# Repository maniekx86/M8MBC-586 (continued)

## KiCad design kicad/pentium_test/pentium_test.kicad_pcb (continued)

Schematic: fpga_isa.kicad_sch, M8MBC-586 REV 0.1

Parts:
C801, C802, C803, C804, C805, C806, C807, C808, C809, C810, C811, C815, C816, C817, C818, C819, C820: 100n; C_0603_1608Metric
C812, C813, C814: 1u; C_0805_2012Metric
C821, C822: 4.7u; C_0603_1608Metric
C823: 22u; C_1206_3216Metric
C824: 47u; CP_Radial_D5.0mm_P2.50mm
R801, R802: 33; R_0603_1608Metric
TP801: FPGA_ISA_SPARE1; TestPoint_Pad_D1.0mm
TP802: FPGA_ISA_SPARE6; TestPoint_Pad_D1.0mm
TP803: FPGA_ISA_SPARE2; TestPoint_Pad_D1.0mm
TP804: FPGA_ISA_SPARE7; TestPoint_Pad_D1.0mm
TP805: FPGA_ISA_SPARE3; TestPoint_Pad_D1.0mm
TP806: FPGA_ISA_SPARE8; TestPoint_Pad_D1.0mm
TP807: FPGA_ISA_SPARE4; TestPoint_Pad_D1.0mm
TP809: FPGA_ISA_SPARE5; TestPoint_Pad_D1.0mm
TP810: ISA_VCCINT; TestPoint_Pad_D1.0mm
U801: XC6SLX9-FTG256; Xilinx_FTG256
U802: LDL1117S12R; SOT-223-3_TabPin2
Y801: 14.318 MHz; Crystal_SMD_7050-4Pin_7.0x5.0mm

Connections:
+1V2_F3: C817.1, C818.1, C819.1, C820.1, C821.1, C822.1, C823.1, C824.1, TP810.1, U801.G7 (VCCINT), U801.G9 (VCCINT), U801.H8 (VCCINT), U801.H10 (VCCINT), U801.J7 (VCCINT), U801.J9 (VCCINT), U801.K8 (VCCINT), U801.K10 (VCCINT), U802.2 (VO)
+3V3: C801.1, C802.1, C803.1, C804.1, C805.1, C806.1, C807.1, C808.1, C809.1, C810.1, C811.1, C812.1, C813.1, C814.1, C815.1, C816.1, U801.B4 (VCCO_0), U801.B9 (VCCO_0), U801.B13 (VCCO_0), U801.D2 (VCCO_3), U801.D7 (VCCO_0), U801.D10 (VCCO_0), U801.D15 (VCCO_1), U801.E5 (VCCAUX), U801.F8 (VCCAUX), U801.F11 (VCCAUX), U801.G4 (VCCO_3), U801.G10 (VCCAUX), U801.G13 (VCCO_1), U801.H6 (VCCAUX), U801.J2 (VCCO_3), U801.J10 (VCCAUX), U801.J15 (VCCO_1), U801.K4 (VCCO_3), U801.K13 (VCCO_1), U801.L6 (VCCAUX), U801.L9 (VCCAUX), U801.N2 (VCCO_3), U801.N7 (VCCO_2), U801.N10 (VCCO_2), U801.N11 (IO_L13P_M1_2), U801.N15 (VCCO_1), U801.R4 (VCCO_2), U801.R8 (VCCO_2), U801.R13 (VCCO_1), U801.T11 (IO_L1N_M0_CMPMISO_2), U802.3 (VI), Y801.4 (Vdd); also elsewhere on the board
/fpga_isa/FPGA_ISA_SPARE1: TP801.1, U801.B3 (IO_L83P_3)
/fpga_isa/FPGA_ISA_SPARE2: TP803.1, U801.A3 (IO_L83N_VREF_3)
/fpga_isa/FPGA_ISA_SPARE3: TP805.1, U801.A2 (IO_L52N_M3A9_3)
/fpga_isa/FPGA_ISA_SPARE4: TP807.1, U801.B2 (IO_L52P_M3A8_3)
/fpga_isa/FPGA_ISA_SPARE5: TP809.1, U801.B1 (IO_L50N_M3BA2_3)
/fpga_isa/FPGA_ISA_SPARE6: TP802.1, U801.C1 (IO_L50P_M3WE_3)
/fpga_isa/FPGA_ISA_SPARE7: TP804.1, U801.C2 (IO_L48N_M3BA1_3)
/fpga_isa/FPGA_ISA_SPARE8: TP806.1, U801.C3 (IO_L48P_M3BA0_3)
/fpga_isa/ISA_FPGA_OSC: R802.2, U801.J16 (IO_L43N_GCLK4_M1DQ5_1)
A20M#: U801.C16 (IO_L33N_A14_M1A4_1); also elsewhere on the board
FPGA_ISA_CCLK: U801.R11 (IO_L1P_CCLK_2); also elsewhere on the board
FPGA_ISA_DIN: U801.P10 (IO_L3P_D0_DIN_MISO_MISO1_2); also elsewhere on the board
FPGA_ISA_DONE: U801.P13 (DONE_2); also elsewhere on the board
FPGA_ISA_INIT: U801.R3 (IO_L65P_INIT_B_2); also elsewhere on the board
FPGA_ISA_PROGRAM: U801.T2 (PROGRAM_B_2); also elsewhere on the board
GND: C801.2, C802.2, C803.2, C804.2, C805.2, C806.2, C807.2, C808.2, C809.2, C810.2, C811.2, C812.2, C813.2, C814.2, C815.2, C816.2, C817.2, C818.2, C819.2, C820.2, C821.2, C822.2, C823.2, C824.2, U801.A1 (GND), U801.A16 (GND), U801.B7 (GND), U801.B11 (GND), U801.D4 (GND), U801.D13 (GND), U801.E9 (GND), U801.G2 (GND), U801.G8 (GND), U801.G15 (GND), U801.H7 (GND), U801.H9 (GND), U801.H12 (GND), U801.J5 (GND), U801.J8 (GND), U801.K7 (GND), U801.K9 (GND), U801.L2 (GND), U801.L15 (GND), U801.M8 (GND), U801.N13 (GND), U801.P3 (GND), U801.P14 (SUSPEND), U801.R6 (GND), U801.R10 (GND), U801.T1 (GND), U801.T16 (GND), U802.1 (GND), Y801.2 (GND); also elsewhere on the board
INIT: U801.A14 (IO_L65N_SCP2_0); also elsewhere on the board
INTR: U801.B16 (IO_L29N_A22_M1A14_1); also elsewhere on the board
ISA_A0: U801.P6 (IO_L47P_2); also elsewhere on the board
ISA_A1: U801.N6 (IO_L64N_D9_2); also elsewhere on the board
ISA_A2: U801.P5 (IO_L49N_D4_2); also elsewhere on the board
ISA_A3: U801.N5 (IO_L49P_D3_2); also elsewhere on the board
ISA_A4: U801.M5 (IO_L2P_3); also elsewhere on the board
ISA_A5: U801.N4 (IO_L2N_3); also elsewhere on the board
ISA_A6: U801.M4 (IO_L1P_3); also elsewhere on the board
ISA_A7: U801.L5 (IO_L45N_M3ODT_3); also elsewhere on the board
ISA_A8: U801.M3 (IO_L1N_VREF_3); also elsewhere on the board
ISA_A9: U801.L4 (IO_L45P_M3A3_3); also elsewhere on the board
ISA_A10: U801.L3 (IO_L36P_M3DQ8_3); also elsewhere on the board
ISA_A11: U801.L8 (IO_L62P_D5_2); also elsewhere on the board
ISA_A12: U801.K3 (IO_L42P_GCLK25_TRDY2_M3UDM_3); also elsewhere on the board
ISA_A13: U801.J4 (IO_L42N_GCLK24_M3LDM_3); also elsewhere on the board
ISA_A14: U801.J3 (IO_L38P_M3DQ2_3); also elsewhere on the board
ISA_A15: U801.K5 (IO_L47P_M3A0_3); also elsewhere on the board
ISA_A16: U801.K6 (IO_L47N_M3A1_3); also elsewhere on the board
ISA_A17: U801.J6 (IO_L43P_GCLK23_M3RASN_3); also elsewhere on the board
ISA_A18: U801.H5 (IO_L43N_GCLK22_IRDY2_M3CASN_3); also elsewhere on the board
ISA_A19: U801.H3 (IO_L44N_GCLK20_M3A6_3); also elsewhere on the board
ISA_AEN: U801.K12 (IO_L42P_GCLK7_M1UDM_1); also elsewhere on the board
ISA_ALE: U801.P12 (IO_L12N_D2_MISO3_2); also elsewhere on the board
ISA_CLK: U801.T13 (IO_L51N_M1DQ13_1); also elsewhere on the board
ISA_D0: U801.P2 (IO_L33P_M3DQ12_3); also elsewhere on the board
ISA_D1: U801.P1 (IO_L33N_M3DQ13_3); also elsewhere on the board
ISA_D2: U801.N3 (IO_L34P_M3UDQS_3); also elsewhere on the board
ISA_D3: U801.N1 (IO_L34N_M3UDQSN_3); also elsewhere on the board
ISA_D4: U801.M1 (IO_L35N_M3DQ11_3); also elsewhere on the board
ISA_D5: U801.J1 (IO_L38N_M3DQ3_3); also elsewhere on the board
ISA_D6: U801.K2 (IO_L37P_M3DQ0_3); also elsewhere on the board
ISA_D7: U801.K1 (IO_L37N_M3DQ1_3); also elsewhere on the board
ISA_D8: U801.L1 (IO_L36N_M3DQ9_3); also elsewhere on the board
ISA_D9: U801.M2 (IO_L35P_M3DQ10_3); also elsewhere on the board
ISA_D10: U801.R1 (IO_L32N_M3DQ15_3); also elsewhere on the board
ISA_D11: U801.R2 (IO_L32P_M3DQ14_3); also elsewhere on the board
ISA_D12: U801.T3 (IO_L65N_CSO_B_2); also elsewhere on the board
ISA_D13: U801.T5 (IO_L48N_RDWR_B_VREF_2); also elsewhere on the board
ISA_D14: U801.T6 (IO_L47N_2); also elsewhere on the board
ISA_D15: U801.R7 (IO_L32P_GCLK29_2); also elsewhere on the board
ISA_DRQ0: U801.J11 (IO_L40P_GCLK11_M1A5_1); also elsewhere on the board
ISA_DRQ1: U801.T10 (IO_L3N_MOSI_CSI_B_MISO0_2); also elsewhere on the board
ISA_DRQ2: U801.R5 (IO_L48P_D7_2); also elsewhere on the board
ISA_DRQ3: U801.M13 (IO_L74P_AWAKE_1); also elsewhere on the board
ISA_DRQ5: U801.L14 (IO_L47P_FWE_B_M1DQ0_1); also elsewhere on the board
ISA_DRQ6: U801.L16 (IO_L47N_LDC_M1DQ1_1); also elsewhere on the board
ISA_DRQ7: U801.K15 (IO_L44P_A3_M1DQ6_1); also elsewhere on the board
ISA_IO_READY: U801.K16 (IO_L44N_A2_M1DQ7_1); also elsewhere on the board
ISA_IRQ2: U801.T4 (IO_L63N_2); also elsewhere on the board
ISA_IRQ3: U801.P8 (IO_L30P_GCLK1_D13_2); also elsewhere on the board
ISA_IRQ4: U801.T8 (IO_L30N_GCLK0_USERCCLK_2); also elsewhere on the board
ISA_IRQ5: U801.R9 (IO_L23P_2); also elsewhere on the board
ISA_IRQ6: U801.T14 (IO_L51P_M1DQ12_1); also elsewhere on the board
ISA_IRQ7: U801.T9 (IO_L23N_2); also elsewhere on the board
ISA_IRQ10: U801.P15 (IO_L48P_HDC_M1DQ8_1); also elsewhere on the board
ISA_IRQ11: U801.N16 (IO_L45N_A0_M1LDQSN_1); also elsewhere on the board
ISA_IRQ12: U801.L13 (IO_L53N_VREF_1); also elsewhere on the board
ISA_IRQ14: U801.M16 (IO_L46N_FOE_B_M1DQ3_1); also elsewhere on the board
ISA_IRQ15: U801.M15 (IO_L46P_FCS_B_M1DQ2_1); also elsewhere on the board
ISA_LA17: U801.M10 (IO_L16N_VREF_2); also elsewhere on the board
ISA_LA18: U801.L7 (IO_L62N_D6_2); also elsewhere on the board
ISA_LA19: U801.P7 (IO_L31P_GCLK31_D14_2); also elsewhere on the board
ISA_LA20: U801.M6 (IO_L64P_D8_2); also elsewhere on the board
ISA_LA21: U801.M7 (IO_L31N_GCLK30_D15_2); also elsewhere on the board
ISA_LA22: U801.N8 (IO_L29N_GCLK2_2); also elsewhere on the board
ISA_LA23: U801.L10 (IO_L16P_2); also elsewhere on the board
ISA_RESET: U801.M9 (IO_L29P_GCLK3_2); also elsewhere on the board
ISA_SBHE: U801.T15 (IO_L50N_M1UDQSN_1); also elsewhere on the board
ISA_SLOT_OSC: R801.2; also elsewhere on the board
ISA_TC: U801.R12 (IO_L52P_M1DQ14_1); also elsewhere on the board
JTAG2_TCK: U801.C14 (TCK); also elsewhere on the board
JTAG2_TDI: U801.C12 (TDI); also elsewhere on the board
JTAG2_TDO: U801.E14 (TDO); also elsewhere on the board
JTAG2_TMS: U801.A15 (TMS); also elsewhere on the board
KEYBOARD_CLK: U801.A8 (IO_L33N_0); also elsewhere on the board
KEYBOARD_DATA: U801.A7 (IO_L6N_0); also elsewhere on the board
MOUSE_CLK: U801.A6 (IO_L4N_0); also elsewhere on the board
MOUSE_DATA: U801.B6 (IO_L4P_0); also elsewhere on the board
NMI: U801.B14 (IO_L65P_SCP3_0); also elsewhere on the board
unnamed: R801.1, R802.1, Y801.3 (OUT)
PCI_AD0: U801.J14 (IO_L43P_GCLK5_M1DQ4_1); also elsewhere on the board
PCI_AD1: U801.J12 (IO_L40N_GCLK10_M1A6_1); also elsewhere on the board
PCI_AD2: U801.H11 (IO_L38N_A4_M1CLKN_1); also elsewhere on the board
PCI_AD3: U801.G11 (IO_L30N_A20_M1A11_1); also elsewhere on the board
PCI_AD4: U801.G12 (IO_L38P_A5_M1CLK_1); also elsewhere on the board
PCI_AD5: U801.H13 (IO_L39P_M1A3_1); also elsewhere on the board
PCI_AD6: U801.F12 (IO_L30P_A21_M1RESET_1); also elsewhere on the board
PCI_AD7: U801.G14 (IO_L36P_A9_M1BA0_1); also elsewhere on the board
PCI_AD8: U801.F13 (IO_L32P_A17_M1A8_1); also elsewhere on the board
PCI_AD9: U801.F10 (IO_L64P_SCP5_0); also elsewhere on the board
PCI_AD10: U801.E13 (IO_L1P_A25_1); also elsewhere on the board
PCI_AD11: U801.E12 (IO_L1N_A24_VREF_1); also elsewhere on the board
PCI_AD12: U801.D14 (IO_L31P_A19_M1CKE_1); also elsewhere on the board
PCI_AD13: U801.F6 (IO_L55P_M3A13_3); also elsewhere on the board
PCI_AD14: U801.C7 (IO_L6P_0); also elsewhere on the board
PCI_AD15: U801.C8 (IO_L38N_VREF_0); also elsewhere on the board
PCI_AD16: U801.D12 (IO_L66N_SCP0_0); also elsewhere on the board
PCI_AD17: U801.D11 (IO_L66P_SCP1_0); also elsewhere on the board
PCI_AD18: U801.C13 (IO_L63P_SCP7_0); also elsewhere on the board
PCI_AD19: U801.E11 (IO_L64N_SCP4_0); also elsewhere on the board
PCI_AD20: U801.G5 (IO_L51N_M3A4_3); also elsewhere on the board
PCI_AD21: U801.F4 (IO_L53P_M3CKE_3); also elsewhere on the board
PCI_AD22: U801.F3 (IO_L53N_M3A12_3); also elsewhere on the board
PCI_AD23: U801.E3 (IO_L54N_M3A11_3); also elsewhere on the board
PCI_AD24: U801.D3 (IO_L49P_M3A7_3); also elsewhere on the board
PCI_AD25: U801.E4 (IO_L54P_M3RESET_3); also elsewhere on the board
PCI_AD26: U801.E6 (IO_L5N_0); also elsewhere on the board
PCI_AD27: U801.G6 (IO_L51P_M3A10_3); also elsewhere on the board
PCI_AD28: U801.D5 (IO_L3P_0); also elsewhere on the board
PCI_AD29: U801.C5 (IO_L3N_0); also elsewhere on the board
PCI_AD30: U801.C6 (IO_L7N_0); also elsewhere on the board
PCI_AD31: U801.D6 (IO_L7P_0); also elsewhere on the board
PCI_PAR: U801.E7 (IO_L36P_GCLK15_0); also elsewhere on the board
PC_SPK: U801.H15 (IO_L37P_A7_M1A0_1); also elsewhere on the board
POWER_REQ: U801.J13 (IO_L41P_GCLK9_IRDY1_M1RASN_1); also elsewhere on the board
RP_SB_LINK_CLK: U801.B5 (IO_L2P_0); also elsewhere on the board
RP_SB_LINK_DATA: U801.A5 (IO_L2N_0); also elsewhere on the board
RTC_AS: U801.H2 (IO_L39P_M3LDQS_3); also elsewhere on the board
SB_CLK: U801.H4 (IO_L44P_GCLK21_M3A5_3); also elsewhere on the board
SB_NB_SPARE: U801.A4 (IO_L1N_VREF_0); also elsewhere on the board
SB_SPARE_1: U801.K14 (IO_L41N_GCLK8_M1CASN_1); also elsewhere on the board
SERIAL_1_CTS: U801.A11 (IO_L39N_0); also elsewhere on the board
SERIAL_1_DCD: U801.A13 (IO_L63N_SCP6_0); also elsewhere on the board
SERIAL_1_DSR: U801.B12 (IO_L62P_0); also elsewhere on the board
SERIAL_1_DTR: U801.A10 (IO_L35N_GCLK16_0); also elsewhere on the board
SERIAL_1_RI: U801.B10 (IO_L35P_GCLK17_0); also elsewhere on the board
SERIAL_1_RTS: U801.A9 (IO_L34N_GCLK18_0); also elsewhere on the board
SERIAL_1_RXD: U801.A12 (IO_L62N_VREF_0); also elsewhere on the board
SERIAL_1_TXD: U801.B8 (IO_L33P_0); also elsewhere on the board
~FERR: U801.D16 (IO_L31N_A18_M1A12_1); also elsewhere on the board
~FPGA_RESET: U801.P4 (IO_L63P_2); also elsewhere on the board
~IDE_CS1FX: U801.G16 (IO_L36N_A8_M1BA1_1); also elsewhere on the board
~IDE_CS3FX: U801.H14 (IO_L39N_M1ODT_1); also elsewhere on the board
~IDE_RESET: U801.H16 (IO_L37N_A6_M1A1_1); also elsewhere on the board
~IDE_TR_DIR: U801.F16 (IO_L35N_A10_M1A2_1); also elsewhere on the board
~IDE_TR_OE: U801.F15 (IO_L35P_A11_M1A7_1); also elsewhere on the board
~IGNNE: U801.B15 (IO_L29P_A23_M1A13_1); also elsewhere on the board
~ISA_DACK0: U801.R16 (IO_L49N_M1DQ11_1); also elsewhere on the board
~ISA_DACK1: U801.M11 (IO_L2N_CMPMOSI_2); also elsewhere on the board
~ISA_DACK2: U801.T12 (IO_L52N_M1DQ15_1); also elsewhere on the board
~ISA_DACK3: U801.M12 (IO_L2P_CMPCLK_2); also elsewhere on the board
~ISA_DACK5: U801.N14 (IO_L45P_A1_M1LDQS_1); also elsewhere on the board
~ISA_DACK6: U801.P16 (IO_L48N_M1DQ9_1); also elsewhere on the board
~ISA_DACK7: U801.M14 (IO_L74N_DOUT_BUSY_1); also elsewhere on the board
~ISA_IOCS16: U801.R15 (IO_L49P_M1DQ10_1); also elsewhere on the board
~ISA_IOR: U801.L12 (IO_L53P_1); also elsewhere on the board
~ISA_IOW: U801.P11 (IO_L13N_D10_2); also elsewhere on the board
~ISA_MEMCS16: U801.R14 (IO_L50P_M1UDQS_1); also elsewhere on the board
~ISA_MEMR: U801.K11 (IO_L42N_GCLK6_TRDY1_M1LDM_1); also elsewhere on the board
~ISA_MEMW: U801.N12 (IO_L12P_D1_MISO2_2); also elsewhere on the board
~ISA_NOWS: U801.T7 (IO_L32N_GCLK28_2); also elsewhere on the board
~ISA_SMEMR: U801.N9 (IO_L14P_D11_2); also elsewhere on the board
~ISA_SMEMW: U801.P9 (IO_L14N_D12_2); also elsewhere on the board
~PCI_CBE0: U801.F14 (IO_L32N_A16_M1A9_1); also elsewhere on the board
~PCI_CBE1: U801.D8 (IO_L38P_0); also elsewhere on the board
~PCI_CBE2: U801.C11 (IO_L39P_0); also elsewhere on the board
~PCI_CBE3: U801.F5 (IO_L55N_M3A14_3); also elsewhere on the board
~PCI_DEVSEL: U801.D9 (IO_L40N_0); also elsewhere on the board
~PCI_FRAME: U801.E10 (IO_L37P_GCLK13_0); also elsewhere on the board
~PCI_INT1: U801.E2 (IO_L46P_M3CLK_3); also elsewhere on the board
~PCI_INT2: U801.E1 (IO_L46N_M3CLKN_3); also elsewhere on the board
~PCI_INT3: U801.F2 (IO_L41P_GCLK27_M3DQ4_3); also elsewhere on the board
~PCI_INT4: U801.F1 (IO_L41N_GCLK26_M3DQ5_3); also elsewhere on the board
~PCI_IRDY: U801.C10 (IO_L37N_GCLK12_0); also elsewhere on the board
~PCI_LOCK: U801.F9 (IO_L40P_0); also elsewhere on the board
~PCI_PERR: U801.F7 (IO_L5P_0); also elsewhere on the board
~PCI_RST: U801.G3 (IO_L40P_M3DQ6_3); also elsewhere on the board
~PCI_SERR: U801.E8 (IO_L36N_GCLK14_0); also elsewhere on the board
~PCI_STOP: U801.C9 (IO_L34P_GCLK19_0); also elsewhere on the board
~ROM_OE: U801.H1 (IO_L39N_M3LDQSN_3); also elsewhere on the board
~RTC_CS: U801.G1 (IO_L40N_M3DQ7_3); also elsewhere on the board
~RTC_IRQ: U801.D1 (IO_L49N_M3A2_3); also elsewhere on the board
~SB_GNT: U801.E16 (IO_L34N_A12_M1BA2_1); also elsewhere on the board
~SB_REQ: U801.E15 (IO_L34P_A13_M1WE_1); also elsewhere on the board
~SMI: U801.C15 (IO_L33P_A15_M1A10_1); also elsewhere on the board
~STPCLK: U801.C4 (IO_L1P_HSWAPEN_0); also elsewhere on the board

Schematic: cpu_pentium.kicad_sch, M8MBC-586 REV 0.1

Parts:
C201, C202, C203, C204, C205, C206, C207, C208, C209, C210, C211, C212, C213, C214, C215, C216, C217, C218, C219, C220, C221, C222, C223, C224: 100n; C_0603_1608Metric
C225, C226, C249, C250: 220u; CP_Radial_D6.3mm_P2.50mm
C227, C228, C229, C230, C231, C232, C233, C234, C235, C236, C237, C238, C239, C240, C241, C242, C243: 1u; C_0805_2012Metric
C244, C245, C246, C247, C248: 4.7u; C_0805_2012Metric
C251, C252, C253, C254, C255: 22u; C_1206_3216Metric
C256, C257, C258, C259: 10u; C_1206_3216Metric
J201: Bus speed; PinHeader_2x03_P2.54mm_Vertical
JP201: Jumper_3_Open; PinHeader_1x03_P2.54mm_Vertical
R201: 4.7K; R_0603_1608Metric
RN201, RN202, RN203, RN204: 4.7K; R_Array_Convex_4x0603
TP201: CPU_TMS; TestPoint_Pad_D1.0mm
TP202: CPU_TDO; TestPoint_Pad_D1.0mm
TP203: CPU_TDI; TestPoint_Pad_D1.0mm
TP204: CPU_TCK; TestPoint_Pad_D1.0mm
U201: PGA321; PGA-321

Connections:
+3V3: C201.1, C202.1, C203.1, C204.1, C205.1, C206.1, C207.1, C208.1, C209.1, C210.1, C236.1, C237.1, C238.1, C239.1, C240.1, C241.1, C242.1, C243.1, C249.1, C250.1, C256.1, C257.1, C258.1, C259.1, J201.2, J201.4, J201.6, JP201.1 (A), R201.2, RN201.5 (R4.2), RN201.6 (R3.2), RN201.7 (R2.2), RN201.8 (R1.2), RN202.5 (R4.2), RN202.6 (R3.2), RN202.7 (R2.2), RN202.8 (R1.2), RN204.5 (R4.2), RN204.6 (R3.2), RN204.7 (R2.2), RN204.8 (R1.2), U201.A19 (VCC3[32]), U201.A21 (VCC3[32]), U201.A23 (VCC3[32]), U201.A25 (VCC3[32]), U201.A27 (VCC3[32]), U201.A29 (VCC3[32]), U201.AA37 (VCC3[32]), U201.AC37 (VCC3[32]), U201.AE37 (VCC3[32]), U201.AG37 (VCC3[32]), U201.AJ19 (VCC3[32]), U201.AJ29 (VCC3[32]), U201.AN21 (VCC3[32]), U201.AN23 (VCC3[32]), U201.AN25 (VCC3[32]), U201.AN27 (VCC3[32]), U201.AN29 (VCC3[32]), U201.E21 (VCC3[32]), U201.E27 (VCC3[32]), U201.E37 (VCC3[32]), U201.G37 (VCC3[32]), U201.J37 (VCC3[32]), U201.L33 (VCC3[32]), U201.L37 (VCC3[32]), U201.N37 (VCC3[32]), U201.Q37 (VCC3[32]), U201.S37 (VCC3[32]), U201.T34 (VCC3[32]), U201.U33 (VCC3[32]), U201.U37 (VCC3[32]), U201.W37 (VCC3[32]), U201.Y37 (VCC3[32]); also elsewhere on the board
/cpu_pentium/AP: RN204.4 (R4.1), U201.AK02 (AP)
/cpu_pentium/WB/~WT: JP201.2 (C), U201.AA05 (WB/WT#)
/cpu_pentium/~FRCMC: RN204.2 (R2.1), U201.Y35 (FRCMC#1)
/cpu_pentium/~PEN: RN204.3 (R3.1), U201.Z34 (PEN#)
/cpu_pentium/~TRST: RN204.1 (R1.1), U201.Q33 (TRST#)
A20M#: U201.AK08 (A20M#); also elsewhere on the board
AHOLD: U201.V04 (AHOLD); also elsewhere on the board
CPU_CLK: U201.AK18 (CLK); also elsewhere on the board
CPU_RESET: R201.1, U201.AK20 (RESET); also elsewhere on the board
C_A3: U201.AL35 (A3); also elsewhere on the board
C_A4: U201.AM34 (A4); also elsewhere on the board
C_A5: U201.AK32 (A5); also elsewhere on the board
C_A6: U201.AN33 (A6); also elsewhere on the board
C_A7: U201.AL33 (A7); also elsewhere on the board
C_A8: U201.AM32 (A8); also elsewhere on the board
C_A9: U201.AK30 (A9); also elsewhere on the board
C_A10: U201.AN31 (A10); also elsewhere on the board
C_A11: U201.AL31 (A11); also elsewhere on the board
C_A12: U201.AL29 (A12); also elsewhere on the board
C_A13: U201.AK28 (A13); also elsewhere on the board
C_A14: U201.AL27 (A14); also elsewhere on the board
C_A15: U201.AK26 (A15); also elsewhere on the board
C_A16: U201.AL25 (A16); also elsewhere on the board
C_A17: U201.AK24 (A17); also elsewhere on the board
C_A18: U201.AL23 (A18); also elsewhere on the board
C_A19: U201.AK22 (A19); also elsewhere on the board
C_A20: U201.AL21 (A20); also elsewhere on the board
C_A21: U201.AF34 (A21); also elsewhere on the board
C_A22: U201.AH36 (A22); also elsewhere on the board
C_A23: U201.AE33 (A23); also elsewhere on the board
C_A24: U201.AG35 (A24); also elsewhere on the board
C_A25: U201.AJ35 (A25); also elsewhere on the board
C_A26: U201.AH34 (A26); also elsewhere on the board
C_A27: U201.AG33 (A27); also elsewhere on the board
C_A28: U201.AK36 (A28); also elsewhere on the board
C_A29: U201.AK34 (A29); also elsewhere on the board
C_A30: U201.AM36 (A30); also elsewhere on the board
C_A31: U201.AJ33 (A31); also elsewhere on the board
C_D0: U201.K34 (D0); also elsewhere on the board
C_D1: U201.G35 (D1); also elsewhere on the board
C_D2: U201.J35 (D2); also elsewhere on the board
C_D3: U201.G33 (D3); also elsewhere on the board
C_D4: U201.F36 (D4); also elsewhere on the board
C_D5: U201.F34 (D5); also elsewhere on the board
C_D6: U201.E35 (D6); also elsewhere on the board
C_D7: U201.E33 (D7); also elsewhere on the board
C_D8: U201.D34 (D8); also elsewhere on the board
C_D9: U201.C37 (D9); also elsewhere on the board
C_D10: U201.C35 (D10); also elsewhere on the board
C_D11: U201.B36 (D11); also elsewhere on the board
C_D12: U201.D32 (D12); also elsewhere on the board
C_D13: U201.B34 (D13); also elsewhere on the board
C_D14: U201.C33 (D14); also elsewhere on the board
C_D15: U201.A35 (D15); also elsewhere on the board
C_D16: U201.B32 (D16); also elsewhere on the board
C_D17: U201.C31 (D17); also elsewhere on the board
C_D18: U201.A33 (D18); also elsewhere on the board
C_D19: U201.D28 (D19); also elsewhere on the board
C_D20: U201.B30 (D20); also elsewhere on the board
C_D21: U201.C29 (D21); also elsewhere on the board
C_D22: U201.A31 (D22); also elsewhere on the board
C_D23: U201.D26 (D23); also elsewhere on the board
C_D24: U201.C27 (D24); also elsewhere on the board
C_D25: U201.C23 (D25); also elsewhere on the board
C_D26: U201.D24 (D26); also elsewhere on the board
C_D27: U201.C21 (D27); also elsewhere on the board
C_D28: U201.D22 (D28); also elsewhere on the board
C_D29: U201.C19 (D29); also elsewhere on the board
C_D30: U201.D20 (D30); also elsewhere on the board
C_D31: U201.C17 (D31); also elsewhere on the board
C_D32: U201.C15 (D32); also elsewhere on the board
C_D33: U201.D16 (D33); also elsewhere on the board
C_D34: U201.C13 (D34); also elsewhere on the board
C_D35: U201.D14 (D35); also elsewhere on the board
C_D36: U201.C11 (D36); also elsewhere on the board
C_D37: U201.D12 (D37); also elsewhere on the board
C_D38: U201.C09 (D38); also elsewhere on the board
C_D39: U201.D10 (D39); also elsewhere on the board
C_D40: U201.D08 (D40); also elsewhere on the board
C_D41: U201.A05 (D41); also elsewhere on the board
C_D42: U201.E09 (D42); also elsewhere on the board
C_D43: U201.B04 (D43); also elsewhere on the board
C_D44: U201.D06 (D44); also elsewhere on the board
C_D45: U201.C05 (D45); also elsewhere on the board
C_D46: U201.E07 (D46); also elsewhere on the board
C_D47: U201.C03 (D47); also elsewhere on the board
C_D48: U201.D04 (D48); also elsewhere on the board
C_D49: U201.E05 (D49); also elsewhere on the board
C_D50: U201.D02 (D50); also elsewhere on the board
C_D51: U201.F04 (D51); also elsewhere on the board
C_D52: U201.E03 (D52); also elsewhere on the board
C_D53: U201.G05 (D53); also elsewhere on the board
C_D54: U201.E01 (D54); also elsewhere on the board
C_D55: U201.G03 (D55); also elsewhere on the board
C_D56: U201.H04 (D56); also elsewhere on the board
C_D57: U201.J03 (D57); also elsewhere on the board
C_D58: U201.J05 (D58); also elsewhere on the board
C_D59: U201.K04 (D59); also elsewhere on the board
C_D60: U201.L05 (D60); also elsewhere on the board
C_D61: U201.L03 (D61); also elsewhere on the board
C_D62: U201.M04 (D62); also elsewhere on the board
C_D63: U201.N03 (D63); also elsewhere on the board
GND: C201.2, C202.2, C203.2, C204.2, C205.2, C206.2, C207.2, C208.2, C209.2, C210.2, C211.2, C212.2, C213.2, C214.2, C215.2, C216.2, C217.2, C218.2, C219.2, C220.2, C221.2, C222.2, C223.2, C224.2, C225.2, C226.2, C227.2, C228.2, C229.2, C230.2, C231.2, C232.2, C233.2, C234.2, C235.2, C236.2, C237.2, C238.2, C239.2, C240.2, C241.2, C242.2, C243.2, C244.2, C245.2, C246.2, C247.2, C248.2, C249.2, C250.2, C251.2, C252.2, C253.2, C254.2, C255.2, C256.2, C257.2, C258.2, C259.2, JP201.3 (B), RN203.2 (R2.1), RN203.3 (R3.1), RN203.4 (R4.1), U201.A03 (Vss[68]), U201.AB02 (Vss[68]), U201.AB04 (HOLD), U201.AB36 (Vss[68]), U201.AD02 (Vss[68]), U201.AD36 (Vss[68]), U201.AF02 (Vss[68]), U201.AF36 (Vss[68]), U201.AH02 (Vss[68]), U201.AJ07 (Vss[68]), U201.AJ09 (Vss[68]), U201.AJ13 (Vss[68]), U201.AJ17 (Vss[68]), U201.AJ21 (Vss[68]), U201.AJ25 (Vss[68]), U201.AJ27 (Vss[68]), U201.AJ31 (Vss[68]), U201.AJ37 (Vss[68]), U201.AL37 (Vss[68]), U201.AM08 (Vss[68]), U201.AM10 (Vss[68]), U201.AM12 (Vss[68]), U201.AM14 (Vss[68]), U201.AM16 (Vss[68]), U201.AM18 (Vss[68]), U201.AM20 (Vss[68]), U201.AM22 (Vss[68]), U201.AM24 (Vss[68]), U201.AM26 (Vss[68]), U201.AM28 (Vss[68]), U201.AM30 (Vss[68]), U201.AN37 (Vss[68]), U201.B06 (Vss[68]), U201.B08 (Vss[68]), U201.B10 (Vss[68]), U201.B12 (Vss[68]), U201.B14 (Vss[68]), U201.B16 (Vss[68]), U201.B18 (Vss[68]), U201.B20 (Vss[68]), U201.B22 (Vss[68]), U201.B24 (Vss[68]), U201.B26 (Vss[68]), U201.B28 (Vss[68]), U201.E11 (Vss[68]), U201.E13 (Vss[68]), U201.E19 (Vss[68]), U201.E23 (Vss[68]), U201.E29 (Vss[68]), U201.E31 (Vss[68]), U201.H02 (Vss[68]), U201.H36 (Vss[68]), U201.K02 (Vss[68]), U201.K36 (Vss[68]), U201.M02 (Vss[68]), U201.M36 (Vss[68]), U201.P02 (Vss[68]), U201.P36 (Vss[68]), U201.Q35 (CPUTYP), U201.R02 (Vss[68]), U201.R36 (Vss[68]), U201.T02 (Vss[68]), U201.T36 (Vss[68]), U201.U35 (Vss[68]), U201.V02 (Vss[68]), U201.V36 (Vss[68]), U201.X02 (Vss[68]), U201.X36 (Vss[68]), U201.Z02 (Vss[68]), U201.Z36 (Vss[68]); also elsewhere on the board
INIT: U201.AA33 (INIT); also elsewhere on the board
INTR: U201.AD34 (INTR/LINT0); also elsewhere on the board
NMI: U201.AC33 (NMI/LINT1); also elsewhere on the board
unnamed: J201.1, RN203.7 (R2.2), U201.Y33 ([BF0])
unnamed: J201.3, RN203.6 (R3.2), U201.X34 ([BF1])
unnamed: J201.5, RN203.5 (R4.2), U201.W35 ([BF2])
unnamed: RN201.1 (R1.1), U201.N05 (DP7)
unnamed: RN201.2 (R2.1), U201.F02 (DP6)
unnamed: RN201.3 (R3.1), U201.F06 (DP5)
unnamed: RN201.4 (R4.1), U201.C07 (DP4)
unnamed: RN202.1 (R1.1), U201.D18 (DP3)
unnamed: RN202.2 (R2.1), U201.C25 (DP2)
unnamed: RN202.3 (R3.1), U201.D30 (DP1)
unnamed: RN202.4 (R4.1), U201.D36 (DP0)
unnamed: TP204.1, U201.M34 (TCK)
unnamed: TP203.1, U201.N35 (TDI)
unnamed: TP202.1, U201.N33 (TDO)
unnamed: TP201.1, U201.P34 (TMS)
Vcore: C211.1, C212.1, C213.1, C214.1, C215.1, C216.1, C217.1, C218.1, C219.1, C220.1, C221.1, C222.1, C223.1, C224.1, C225.1, C226.1, C227.1, C228.1, C229.1, C230.1, C231.1, C232.1, C233.1, C234.1, C235.1, C244.1, C245.1, C246.1, C247.1, C248.1, C251.1, C252.1, C253.1, C254.1, C255.1, U201.A07 (VCC2[27]), U201.A09 (VCC2[27]), U201.A11 (VCC2[27]), U201.A13 (VCC2[27]), U201.A15 (VCC2[27]), U201.A17 (VCC2[27]), U201.AA01 (VCC2[27]), U201.AC01 (VCC2[27]), U201.AE01 (VCC2[27]), U201.AG01 (VCC2[27]), U201.AJ11 (VCC2[27]), U201.AN09 (VCC2[27]), U201.AN11 (VCC2[27]), U201.AN13 (VCC2[27]), U201.AN15 (VCC2[27]), U201.AN17 (VCC2[27]), U201.AN19 (VCC2[27]), U201.E15 (VCC2[27]), U201.G01 (VCC2[27]), U201.J01 (VCC2[27]), U201.L01 (VCC2[27]), U201.N01 (VCC2[27]), U201.Q01 (VCC2[27]), U201.S01 (VCC2[27]), U201.U01 (VCC2[27]), U201.W01 (VCC2[27]), U201.Y01 (VCC2[27]); also elsewhere on the board
~ADS: U201.AJ05 (ADS#); also elsewhere on the board
~BE0: U201.AL09 (BE0#); also elsewhere on the board
~BE1: U201.AK10 (BE1#); also elsewhere on the board
~BE2: U201.AL11 (BE2#); also elsewhere on the board
~BE3: U201.AK12 (BE3#); also elsewhere on the board
~BE4: U201.AL13 (BE4#); also elsewhere on the board
~BE5: U201.AK14 (BE5#); also elsewhere on the board
~BE6: U201.AL15 (BE6#); also elsewhere on the board
~BE7: U201.AK16 (BE7#); also elsewhere on the board
~BOFF: U201.Z04 (BOFF#); also elsewhere on the board
~BRDY: U201.X04 (BRDY#); also elsewhere on the board
~CACHE: U201.U03 (CACHE#); also elsewhere on the board
~D/C: U201.AK04 (D/C#); also elsewhere on the board
~EADS: U201.AM04 (EADS#); also elsewhere on the board
~EWBE: U201.W03 (EWBE#); also elsewhere on the board
~FERR: U201.Q05 (FERR#); also elsewhere on the board
~FLUSH: U201.AN07 (FLUSH#); also elsewhere on the board
~HITM: U201.AL05 (HITM#); also elsewhere on the board
~HIT: U201.AK06 (HIT#); also elsewhere on the board
~IGNNE: U201.AA35 (IGNNE#); also elsewhere on the board
~KEN/INV: U201.U05 (INV), U201.W05 (KEN#); also elsewhere on the board
~LOCK: U201.AH04 (LOCK#); also elsewhere on the board
~M/IO: U201.T04 (M/IO#); also elsewhere on the board
~NA: U201.Y05 (NA#); also elsewhere on the board
~SMI_ACT: U201.AG03 (SMIACT#); also elsewhere on the board
~SMI: U201.AB34 (SMI#); also elsewhere on the board
~STPCLK: U201.V34 (STPCLK#); also elsewhere on the board
~W/R: U201.AM06 (W/R#); also elsewhere on the board

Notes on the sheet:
4x 10uF 1206 +3V3
~{HIT} is not very needed for uniprocessor system unlike ~{HITM}, but routing it in case or even for debug
If parity checks are not implemented in the system, the ~{DP/PEN} pins should be tied to Vcc through a pullup resistor and the ~{PCHK} pin may be ignored.
10x 100nF 0603 +3V3
8x 1uF 0805 +3V3
9x 1uF 0805 vcore
CPU type distinguishes the Primary processor from the Dual processor. In a single processor environment, or when the Pentium processor with MMX technology is acting as the Primary processor in a dual processing system, CPUTYP should be strapped to VSS. The Dual processor should have CPUTYP strapped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
VCC2 (core)
14x 100nF 0603 vcore
5x 4.7uF 0805 vcore
5x 22uF 1206 vcore
VCC3 (i/o)

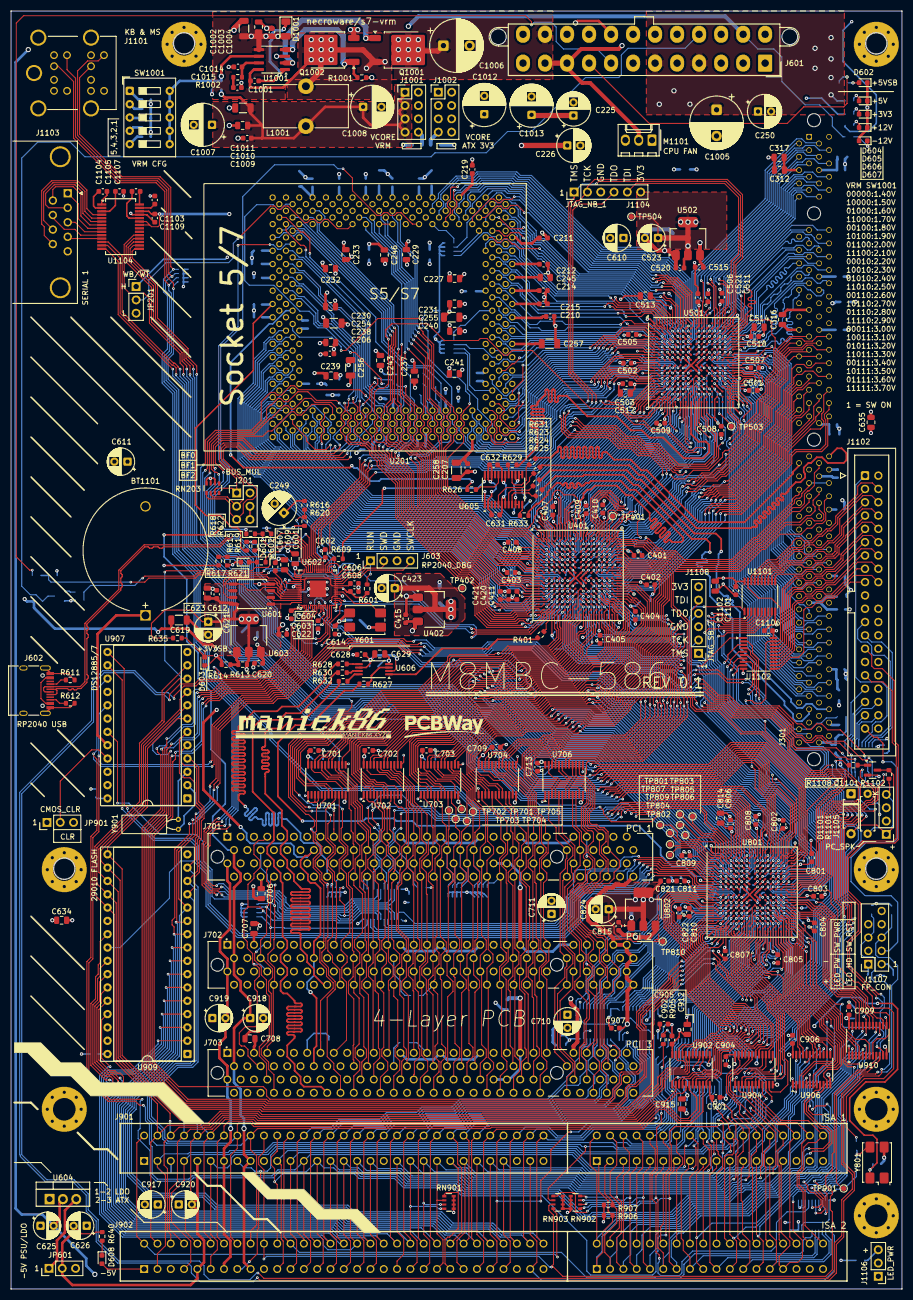
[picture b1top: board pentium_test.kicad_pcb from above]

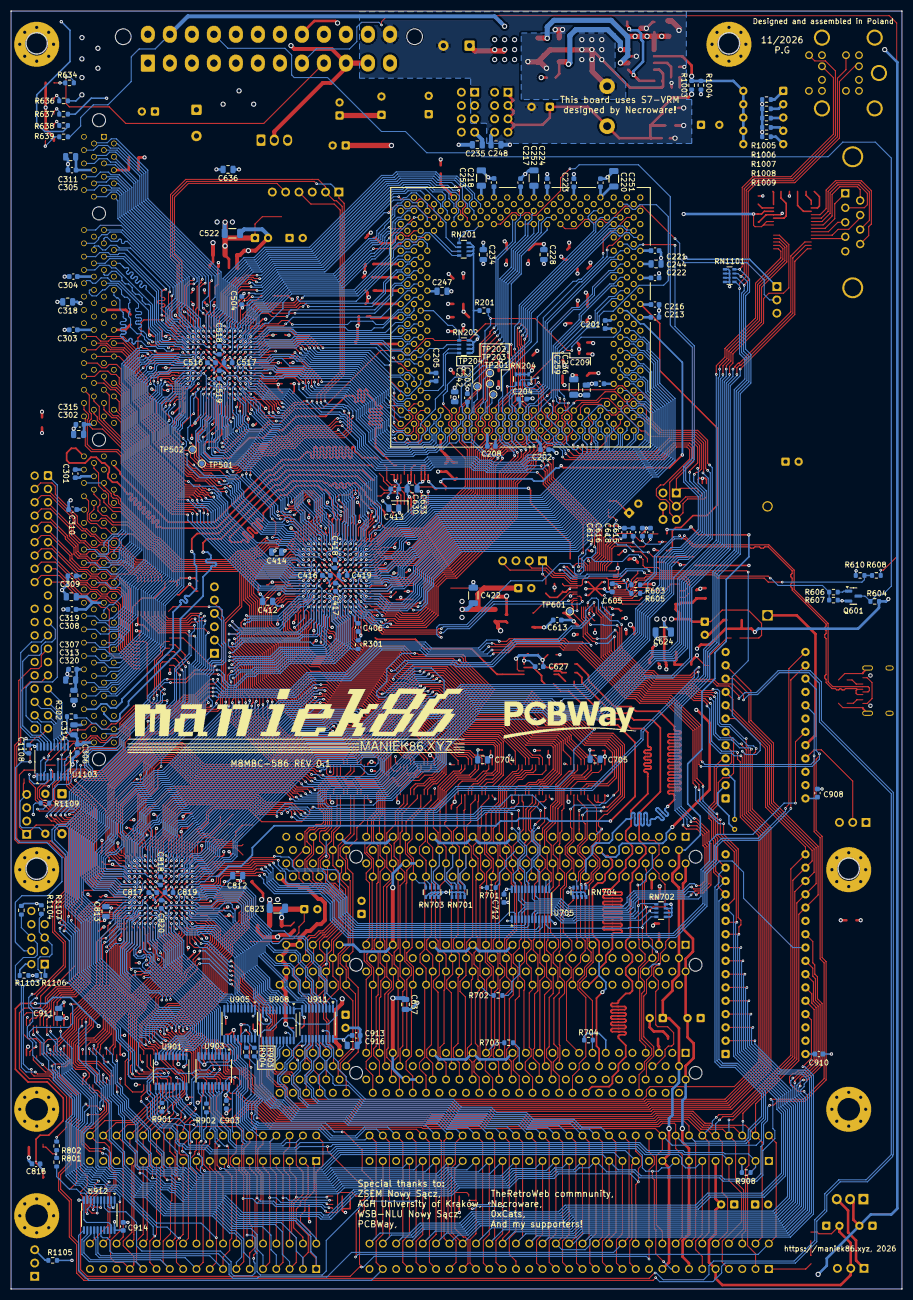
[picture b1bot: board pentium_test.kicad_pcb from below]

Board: 4 copper layers, 170.0 x 243.8 mm, 444 parts (154 on the bottom side), 781 nets.
